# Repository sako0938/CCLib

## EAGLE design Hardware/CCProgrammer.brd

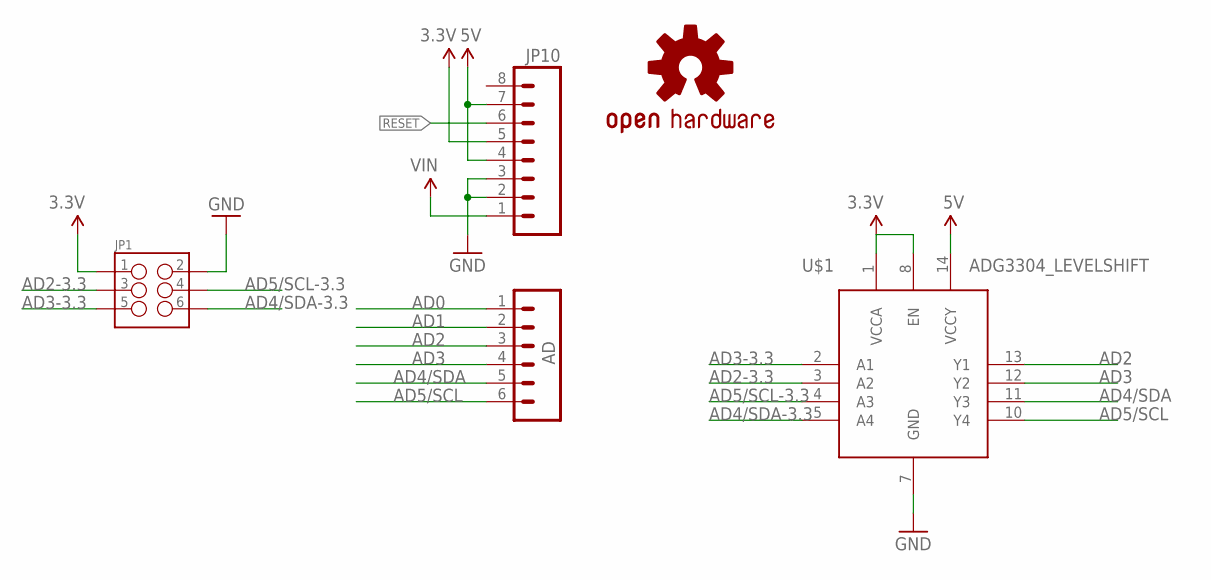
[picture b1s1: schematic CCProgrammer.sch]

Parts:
AD: M06SMD-STRAIGHT-COMBO; 1X06_SMD_STRAIGHT_COMBO
JP1: M03X2SHROUD; 2X3-SHROUDED
JP10: M08SMD-COMBO; 1X08_SMD_COMBINED
LOGO1: OSHW-LOGOM; OSHW-LOGO-M
U$1: ADG3304_LEVELSHIFT; TSSOP14_0.65MM_4.4MM

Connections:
3.3V: JP1.1, JP10.5, U$1.1 (VCCA), U$1.8 (EN)
5V: JP10.4, JP10.7, U$1.14 (VCCY)
AD0: AD.1
AD1: AD.2
AD2: AD.3, U$1.13 (Y1)
AD2-3.3: JP1.3, U$1.3 (A2)
AD3: AD.4, U$1.12 (Y2)
AD3-3.3: JP1.5, U$1.2 (A1)
AD4/SDA: AD.5, U$1.11 (Y3)
AD4/SDA-3.3: JP1.6, U$1.5 (A4)
AD5/SCL: AD.6, U$1.10 (Y4)
AD5/SCL-3.3: JP1.4, U$1.4 (A3)
GND: JP1.2, JP10.2, JP10.3, U$1.7 (GND)
RESET: JP10.6
VIN: JP10.1

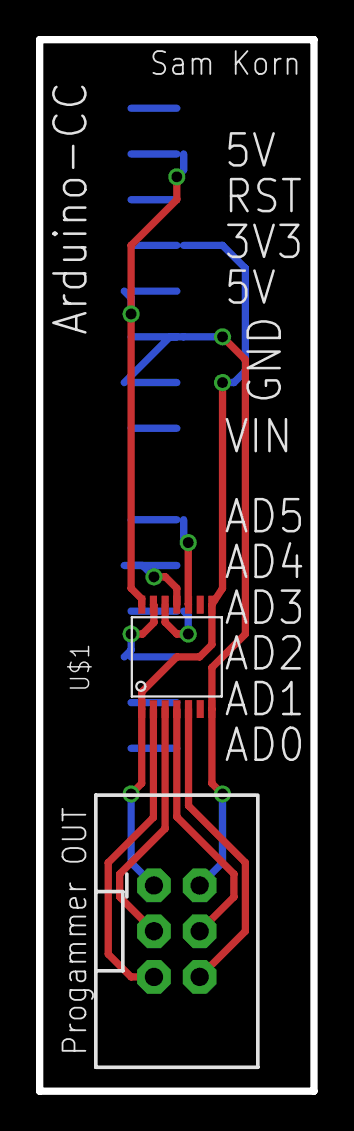
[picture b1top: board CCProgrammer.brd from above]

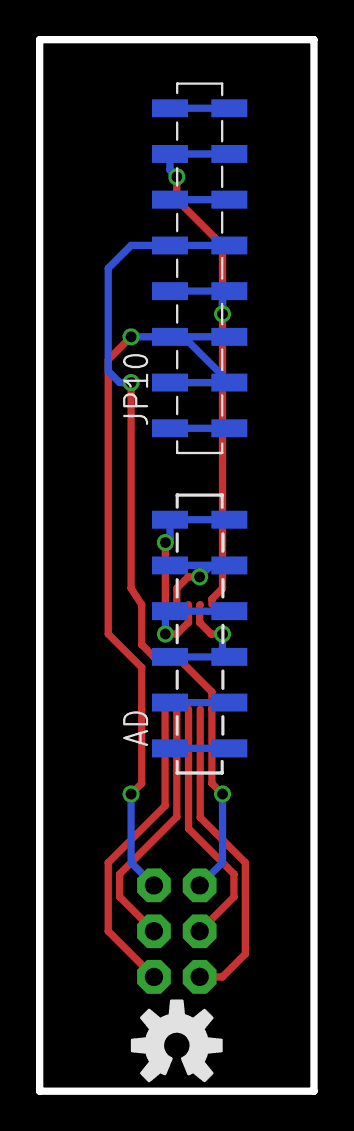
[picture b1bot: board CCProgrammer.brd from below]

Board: 2 copper layers, 15.2 x 58.4 mm, 5 parts (3 on the bottom side), 11 nets.

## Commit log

2015-07-01 First commit of hardware

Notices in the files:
parts and their libraries:
SparkFun-Connectors: Licensing: CC v3.0 Share-Alike You are welcome to use this library for commercial purposes.
